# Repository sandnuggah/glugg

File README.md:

# Glugg

*Glugg* is Swedish for a small opening in a wall. This one keeps an eye on the windows of a wood workshop.

An ESP32-S3 pairs with IKEA MYGGBETT door/window sensors and lights one LED per open window on an 8×8 LED panel. An ESP32-H2 is its Thread radio. It runs fully offline: no Wi-Fi, no app, no cloud.

It runs on a hand-soldered protoboard with two MYGGBETT. The firmware supports up to 64 sensors, one per LED.

## Parts

All from [Electrokit](https://www.electrokit.com/en/quickorder) except the sensors and the LED panel. The same list is in [`bom.csv`](bom.csv) for their quick order form.

| Part | Article no. | Qty |
|---|---|--:|
| Waveshare ESP32-S3-Zero-N8R8, with headers | 41036436 | 1 |
| Waveshare ESP32-H2-Zero, with headers | 41032832 | 1 |
| 8×8 WS2812 LED panel (not from Electrokit) | | 1 |
| 74HCT32 quad OR gate, used as a buffer | 40381032 | 1 |
| DIL socket 18-pin (holds the 74HCT32) | 40410018 | 1 |
| 1N5817 Schottky diode | 40315817 | 1 |
| Resistor 330 Ω | 40811233 | 1 |
| Resistor 1 kΩ | 40811310 | 1 |
| Resistor 10 kΩ | 40811410 | 1 |
| Capacitor 1000 µF 16 V | 41017694 | 1 |
| Capacitor 100 nF | 41015538 | 1 |
| Screw terminal 2.54 mm, 3-pole | 41002454 | 1 |
| Prototype PCB 40×60 mm | 41010656 | 1 |
| IKEA MYGGBETT door/window sensor | from IKEA | up to 64 |

You'll also need a USB-C charger and cable, and solid-core wire.

## Wiring

- Power comes from a USB-C charger plugged into the S3. The S3's 5V pin is the +5 V rail: it feeds the 74HCT32 and the LED panel directly, and the H2's 5V pin through the 1N5817.
- The S3's GPIO13 drives the LEDs through the 74HCT32 (into pins 9 and 10, out of pin 8) and the 330 Ω resistor. Tie the unused inputs to +5 V (pins 1, 2, 12, 13) or GND (pins 4, 5).
- The hole-by-hole protoboard layout is in [`docs/protoboard-small.svg`](docs/protoboard-small.svg) (top) and [`docs/protoboard-small-wiring.svg`](docs/protoboard-small-wiring.svg) (underside).
- The two boards talk over two crossed UART wires, with the 1 kΩ resistor at the S3 end.

A printed carrier board with the same circuit is in [`hardware/pcb/`](hardware/pcb/) (KiCad, rev A, not yet ordered).

## Usage

Plug in the power. A dim white ring breathes out from the middle of the panel for 10–20 seconds while the network starts. Then each sensor's LED shows its window:

| LED | Means |
|---|---|
| Amber | Window open |
| Off | Window closed, or no sensor in this slot |
| Green pulse | Pairing a sensor into this slot |
| Dim white | Sensor paired but hasn't reported yet |
| Blue blink | Sensor not heard from for 2 minutes (battery, range) |

LED 1 is the first LED after the panel's DIN pad; LED 2 onwards follow the panel's data chain. To manage sensors, connect a computer to the S3's USB-C port and open its serial console (for example `idf.py monitor`):

```
pair 3497-011-2332            add a sensor on the lowest free LED
pair 3497-011-2332 slot 14    add a sensor on LED 14
list                          show the paired sensors
move 14 20                    put sensor 14 on LED 20 (swaps if 20 is used)
remove 3                      remove the sensor in slot 3
identify 3                    ask sensor 3 to blink its own light, if it has one
factory-reset confirm         remove every sensor and start over
```

Power and the console share the S3's USB-C port: unplug the charger and plug in the computer instead (Glugg restarts, and the computer powers it meanwhile). A USB-C hub with power pass-through lets you keep both connected.

## Pairing

- Use the 11-digit Matter code printed on the sensor, not the yellow IKEA app code.
- Open the sensor's pairing window first: insert the battery or press its button once. It stays open for 15 minutes.
- Type `pair` and the code, and optionally `slot` and an LED number (1–64). Without a slot, the new sensor takes the lowest free one, so the first sensor gets LED 1.
- A sensor that's already paired somewhere else won't pair again until you factory reset it: hold the button for 10 seconds.
- If `remove` can't reach a sleeping sensor, factory reset it the same way before pairing it again.

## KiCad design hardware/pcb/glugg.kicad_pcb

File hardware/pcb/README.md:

# Glugg carrier board (rev A)

A 70 × 60 mm, 2-layer, through-hole PCB with 3 mm rounded corners that replaces the hand-wired protoboard. It carries exactly the verified protoboard circuit (see `CLAUDE.md`, Wiring), so the firmware is unchanged.

- `glugg.kicad_pro` / `.kicad_sch` / `.kicad_pcb`: the KiCad 9 project. `glugg.kicad_sym` and `glugg.pretty/` hold the two Zero boards' symbols, the 74HCT32 as one block, and the Zero-on-female-headers footprint.
- `fab/`: what to order and build from.
  - `glugg-rev-A-gerbers.zip`: Gerbers and drill files for a PCB maker (2 layers, 1.6 mm).
  - `glugg-rev-A-bom.csv`: parts with Electrokit article numbers.
  - `glugg-schematic.pdf`, `glugg-top.png`, `glugg-bottom.png`: for review.
  - `glugg-1to1-print.pdf`: print at 100 % (no "fit to page") and lay the real parts on it before ordering.

Checks: KiCad ERC 0 violations; DRC with schematic parity 0 violations, 0 unconnected, 0 parity issues.

Both Zero boards sit USB-C up at the top edge; the S3's USB-C is the power input and console, as before. The LED panel connects to J1 (5V, DIN, GND) at the bottom edge.

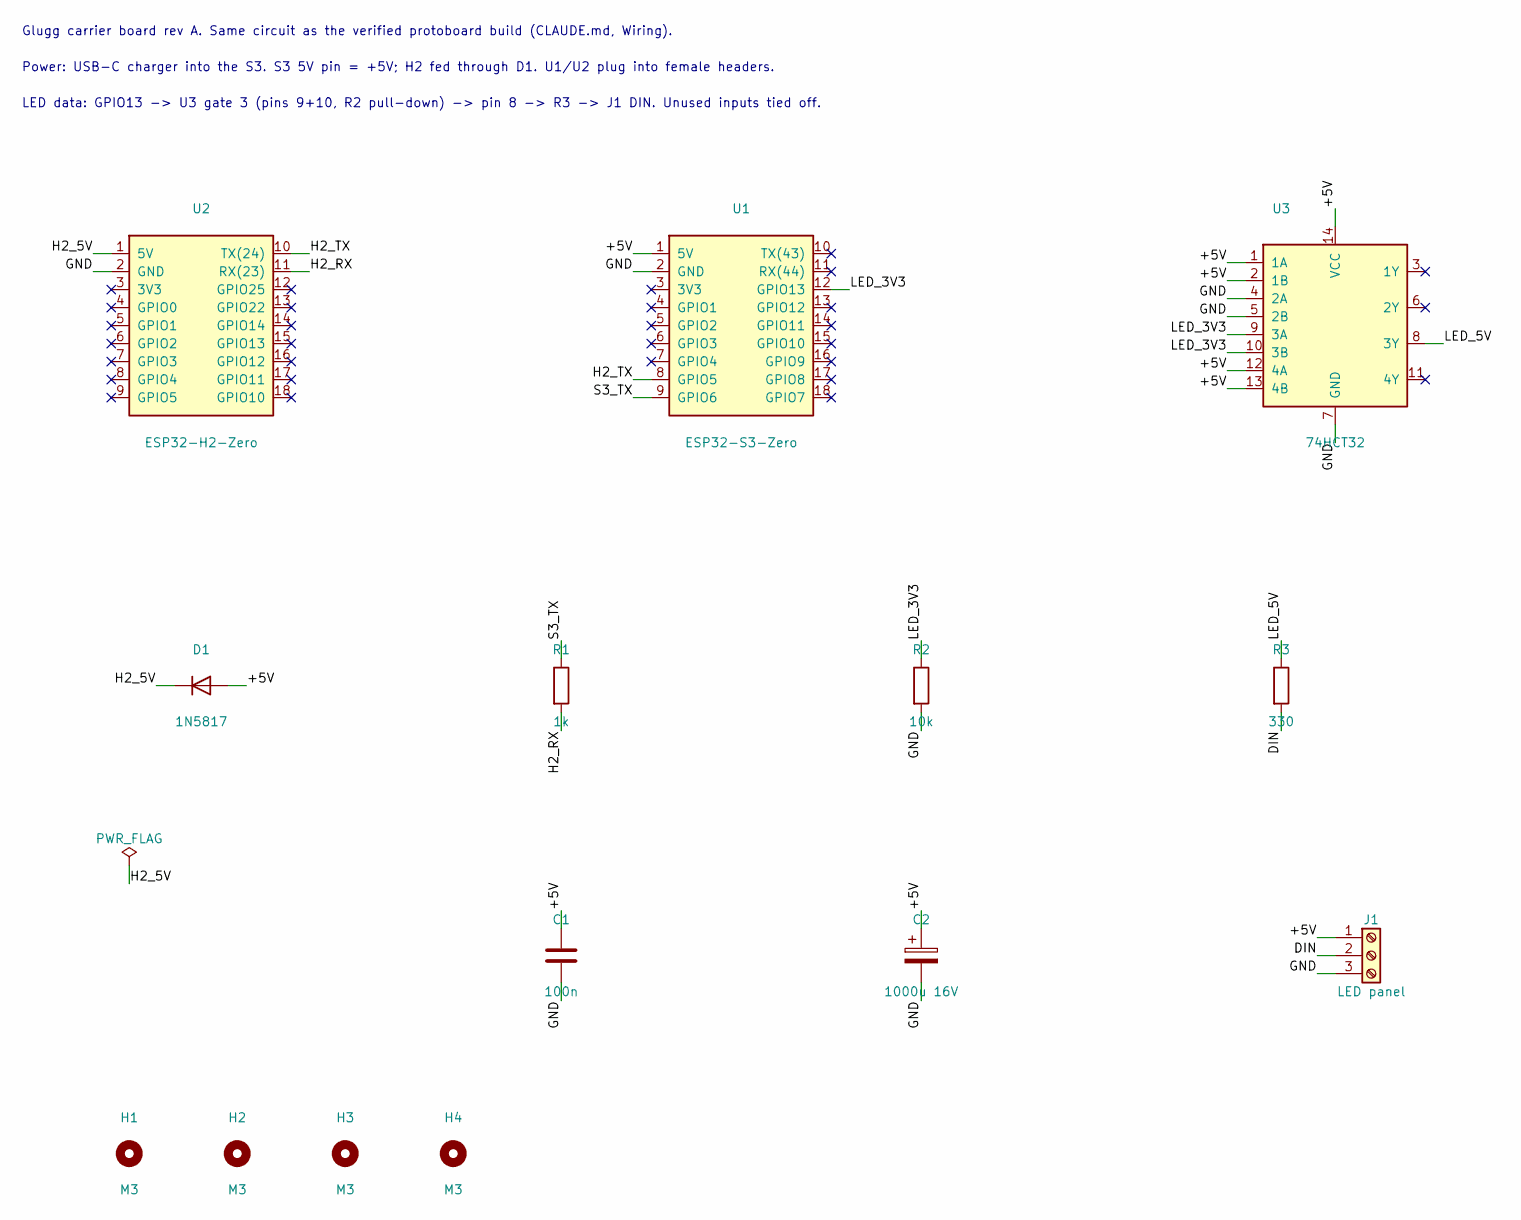
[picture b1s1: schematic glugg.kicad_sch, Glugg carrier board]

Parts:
C1: 100n; C_Disc_D5.0mm_W2.5mm_P5.00mm
C2: 1000u 16V; CP_Radial_D10.0mm_P5.00mm
D1: 1N5817; D_DO-41_SOD81_P10.16mm_Horizontal
H1, H2, H3, H4: M3; MountingHole_3.2mm_M3
J1: LED panel; TerminalBlock_Phoenix_MKDS-1,5-3-5.08_1x03_P5.08mm_Horizont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
R1: 1k; R_Axial_DIN0207_L6.3mm_D2.5mm_P10.16mm_Horizontal
R2: 10k; R_Axial_DIN0207_L6.3mm_D2.5mm_P10.16mm_Horizontal
R3: 330; R_Axial_DIN0207_L6.3mm_D2.5mm_P7.62mm_Horizontal
U1: ESP32-S3-Zero; Waveshare_Zero_Socketed
U2: ESP32-H2-Zero; Waveshare_Zero_Socketed
U3: 74HCT32; DIP-14_W7.62mm_Socket

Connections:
/+5V: C1.1, C2.1, D1.2 (A), J1.1, U1.1 (5V), U3.1 (1A), U3.2 (1B), U3.12 (4A), U3.13 (4B), U3.14 (VCC)
/DIN: J1.2, R3.2
/GND: C1.2, C2.2, J1.3, R2.2, U1.2 (GND), U2.2 (GND), U3.4 (2A), U3.5 (2B), U3.7 (GND)
/H2_5V: D1.1 (K), U2.1 (5V)
/H2_RX: R1.2, U2.11 (RX(23))
/H2_TX: U1.8 (GPIO5), U2.10 (TX(24))
/LED_3V3: R2.1, U1.12 (GPIO13), U3.9 (3A), U3.10 (3B)
/LED_5V: R3.1, U3.8 (3Y)
/S3_TX: R1.1, U1.9 (GPIO6)

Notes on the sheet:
Glugg carrier board rev A. Same circuit as the verified protoboard build (CLAUDE.md, Wiring).
Power: USB-C charger into the S3. S3 5V pin = +5V; H2 fed through D1. U1/U2 plug into female headers.
LED data: GPIO13 -> U3 gate 3 (pins 9+10, R2 pull-down) -> pin 8 -> R3 -> J1 DIN. Unused inputs tied off.

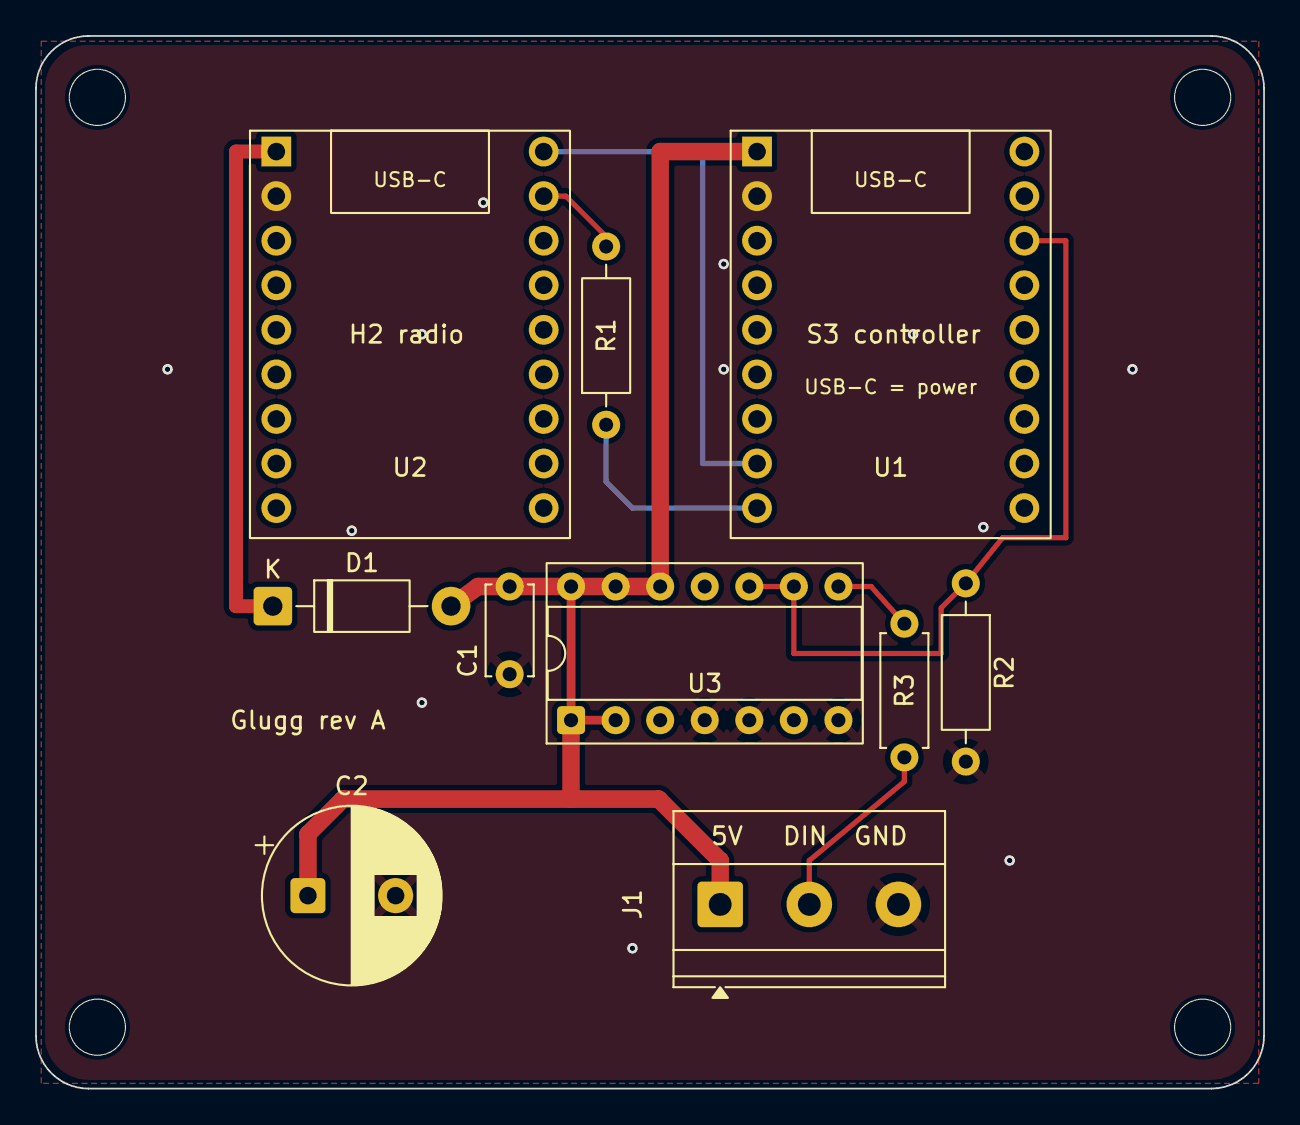
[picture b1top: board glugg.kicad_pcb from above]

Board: 2 copper layers, 70.0 x 60.0 mm, 14 parts (0 on the bottom side), 9 nets.

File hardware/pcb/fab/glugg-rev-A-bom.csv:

Ref;Qty;Part;Electrokit;Note
U1;1;Waveshare ESP32-S3-Zero-N8R8 with headers;41036436;Plugs into two 9-pin female headers
U2;1;Waveshare ESP32-H2-Zero with headers;41032832;Plugs into two 9-pin female headers
U1/U2;1;Female header 2.54 mm 1x40;41003010;Cut into four 1x9 strips (each cut costs one position)
U3;1;74HCT32 DIP-14 (SN74HCT32N);40381032;Gate 3 buffers the LED data; not a plain 74HC32
U3;1;DIL socket 14-pin;40410014;
D1;1;1N5817 Schottky diode;40315817;Band (cathode) towards the silkscreen K, left
R1;1;Resistor 1 kOhm metal film;40811310;Bands: brown black black brown brown
R2;1;Resistor 10 kOhm metal film;40811410;Bands: brown black black red brown
R3;1;Resistor 330 Ohm metal film;40811233;Bands: orange orange black black brown; 7.62 mm pitch
C1;1;Ceramic capacitor 100 nF 5 mm;41015538;
C2;1;Electrolytic capacitor 1000 uF 16 V 10x16 mm;41017694;Stripe (minus) away from the + mark
J1;1;Pluggable screw terminal 5.08 mm 3-pole, male header (board side);41032970;Check its pins fit and its plug faces the bottom edge (1:1 print)
J1;1;Pluggable screw terminal 5.08 mm 3-pole, female plug (wire side);40210012;Takes the LED panel's 5V / DIN / GND wires
H1-H4;4;M3 screws and standoffs;;For the enclosure
